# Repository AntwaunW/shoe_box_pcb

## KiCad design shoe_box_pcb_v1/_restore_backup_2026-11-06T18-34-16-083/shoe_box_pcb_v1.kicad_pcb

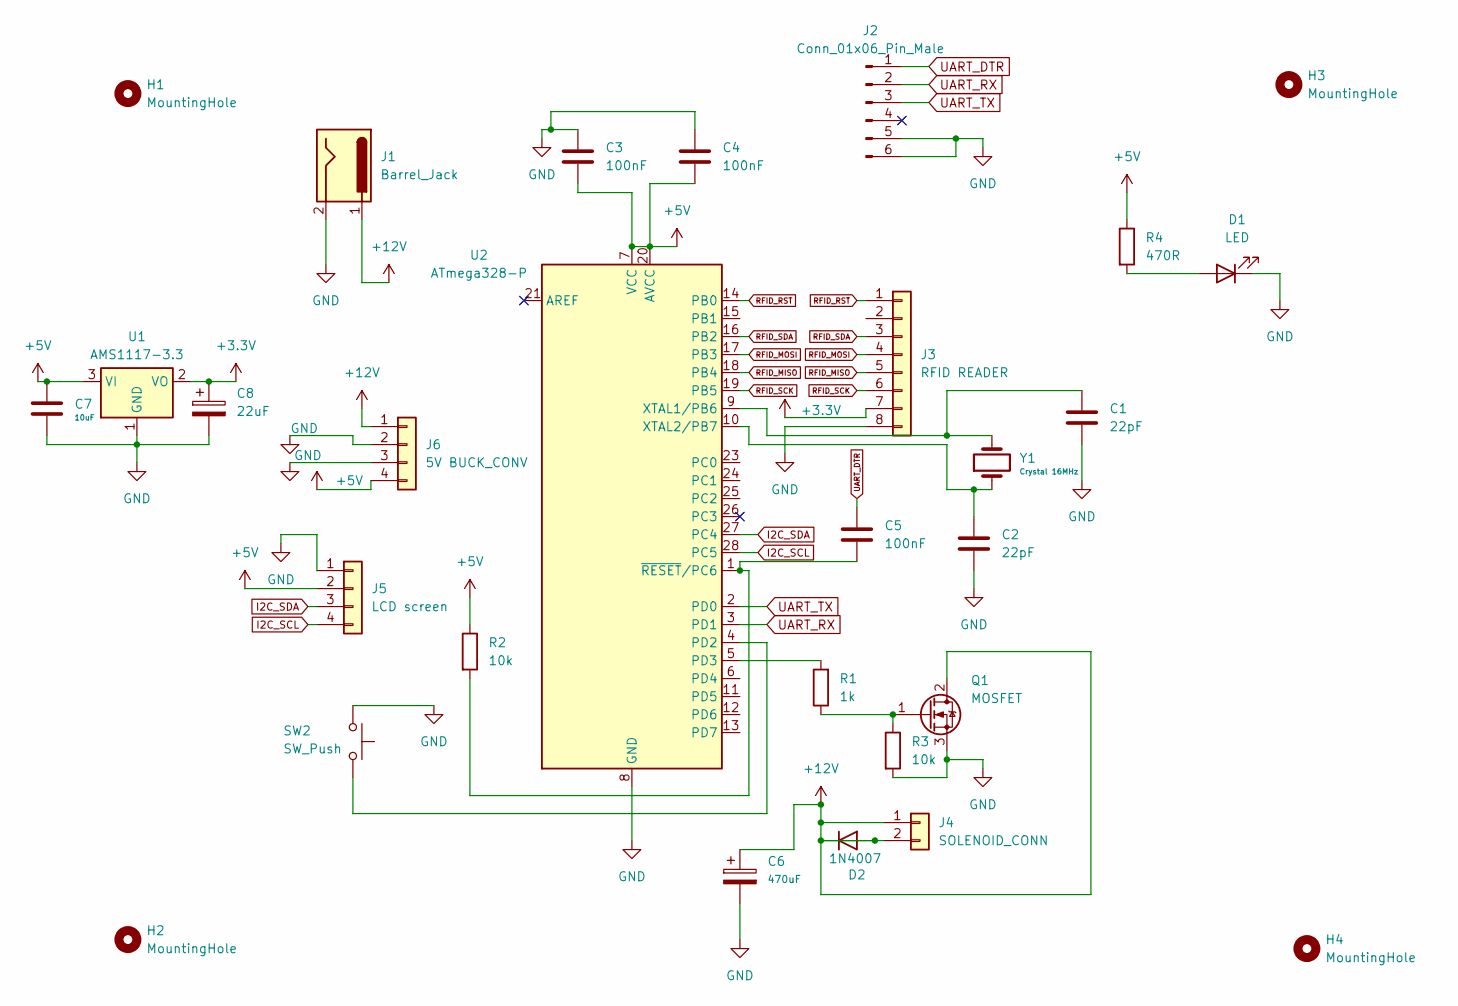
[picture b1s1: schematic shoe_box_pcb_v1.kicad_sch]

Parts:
C1, C2: 22pF; C_Disc_D5.0mm_W2.5mm_P2.50mm
C3, C4, C5: 100nF; C_Disc_D5.0mm_W2.5mm_P2.50mm
C6: 470uF; CP_Radial_D8.0mm_P3.50mm
C7: 10uF; C_Disc_D5.0mm_W2.5mm_P2.50mm
C8: 22uF; CP_Radial_D5.0mm_P2.00mm
D1: LED; LED_D5.0mm
D2: 1N4007; D_DO-41_SOD81_P10.16mm_Horizontal
H1, H2, H3, H4: MountingHole; MountingHole_3.2mm_M3
J1: Barrel_Jack; BarrelJack_CUI_PJ-063AH_Horizontal
J2: Conn_01x06_Pin_Male; PinHeader_1x06_P2.54mm_Vertical
J3: RFID READER; PinHeader_1x07_P2.54mm_Vertical
J4: SOLENOID_CONN; PinHeader_1x02_P2.54mm_Vertical
J5: LCD screen; PinHeader_1x04_P2.54mm_Vertical
J6: 5V BUCK_CONV; PinHeader_1x04_P2.54mm_Vertical
Q1: MOSFET; TO-220-3_Vertical
R1: 1k; R_Axial_DIN0207_L6.3mm_D2.5mm_P7.62mm_Horizontal
R2, R3: 10k; R_Axial_DIN0207_L6.3mm_D2.5mm_P7.62mm_Horizontal
R4: 470R; R_Axial_DIN0207_L6.3mm_D2.5mm_P7.62mm_Horizontal
SW2: SW_Push; PinHeader_1x02_P2.54mm_Vertical
U1: AMS1117-3.3; SOT-223-3_TabPin2
U2: ATmega328-P; DIP-28_W7.62mm
Y1: Crystal 16MHz; Crystal_HC49-4H_Vertical

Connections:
+3.3V: C8.1, J3.7, U1.2 (VO)
+5V: C3.2, C4.2, C7.1, J5.2, J6.4, R2.1, R4.1, U1.3 (VI), U2.7 (VCC), U2.20 (AVCC)
+12V: C6.1, D2.1 (K), D2.2 (A), J1.1, J4.1, J4.2, J6.1, Q1.2 (D)
GND: C1.2, C2.2, C3.1, C4.1, C6.2, C7.2, C8.2, D1.1 (K), J1.2, J2.5, J2.6, J3.8, J5.1, J6.2, J6.3, Q1.3 (S), R3.2, SW2.1, U1.1 (GND), U2.8 (GND), U2.22 (GND)
I2C_SCL: J5.4, U2.28 (PC5)
I2C_SDA: J5.3, U2.27 (PC4)
unnamed: D1.2 (A), R4.2
unnamed: Q1.1 (G), R1.1, R3.1
unnamed: SW2.2, U2.4 (PD2)
unnamed: R1.2, U2.5 (PD3)
unnamed: C1.1, U2.9 (XTAL1/PB6), Y1.2
unnamed: C2.1, U2.10 (XTAL2/PB7), Y1.1
unnamed: C5.2, R2.2, U2.1 (~RESET/PC6)
RFID_MISO: J3.5, U2.18 (PB4)
RFID_MOSI: J3.4, U2.17 (PB3)
RFID_RST: J3.1, U2.14 (PB0)
RFID_SCK: J3.6, U2.19 (PB5)
RFID_SDA: J3.3, U2.16 (PB2)
UART_DTR: C5.1, J2.1
UART_RX: J2.2, U2.3 (PD1)
UART_TX: J2.3, U2.2 (PD0)

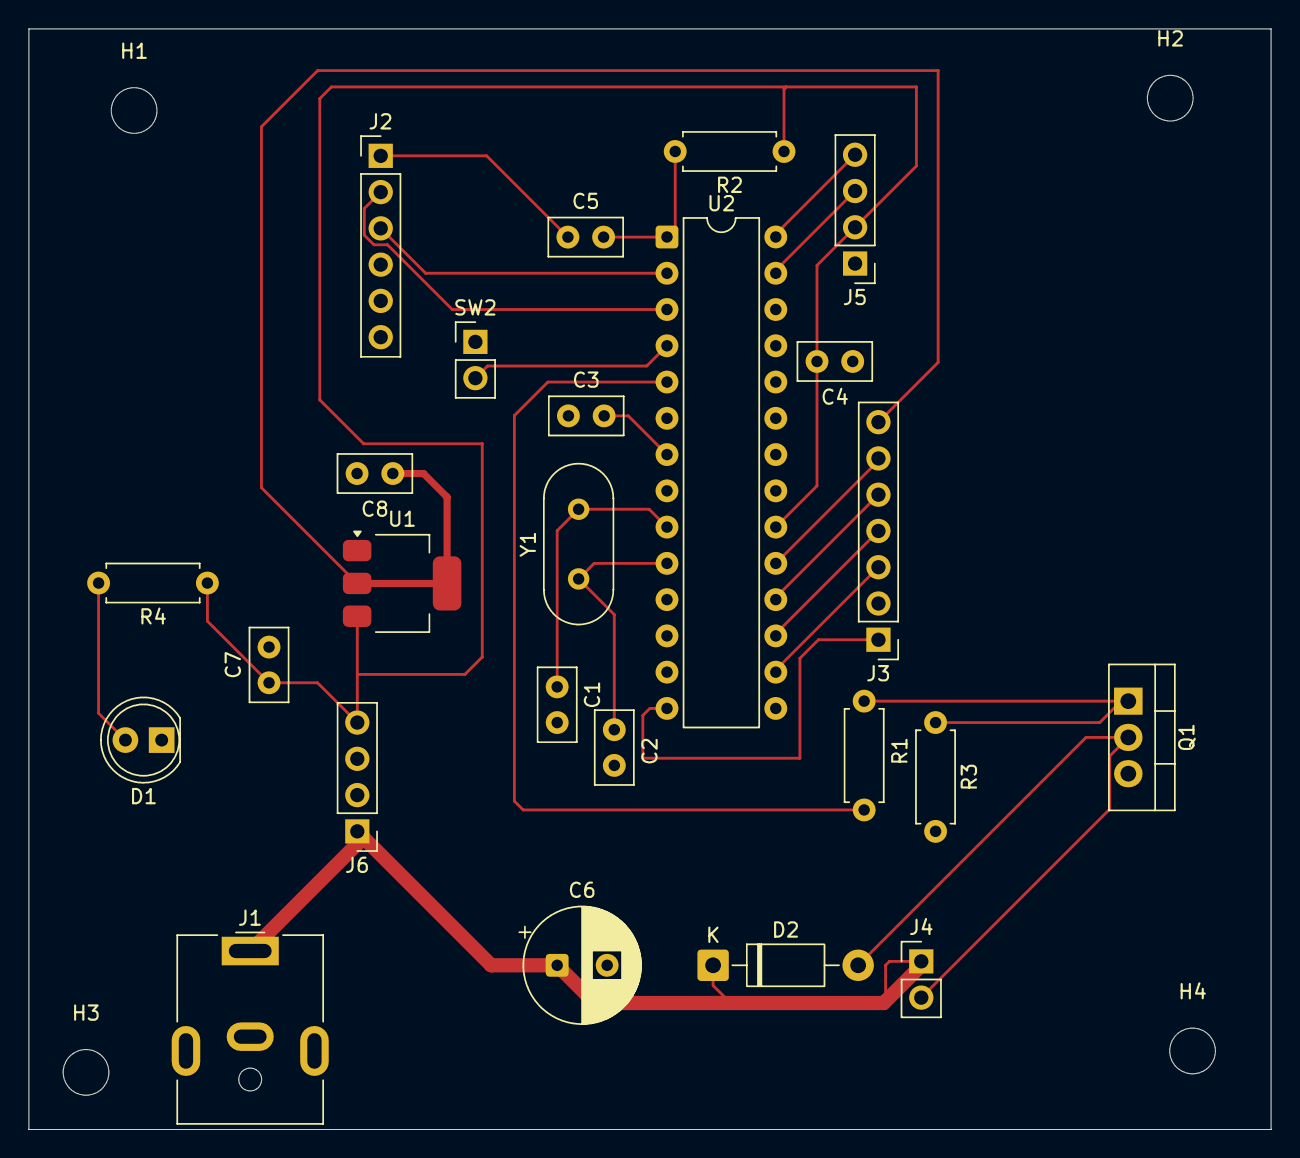
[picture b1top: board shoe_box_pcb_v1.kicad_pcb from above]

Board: 2 copper layers, 87.0 x 77.1 mm, 29 parts (0 on the bottom side), 21 nets.
